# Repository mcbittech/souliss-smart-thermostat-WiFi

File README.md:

# souliss-smart-thermostat-WiFi

Wi-Fi Smart Thermostat based on Souliss IoT Framework

Youtube video:
https://youtu.be/Pk9kK5DvYXE

[Wiki-How to Compile & Upload](https://github.com/mcbittech/souliss-smart-thermostat-WiFi/wiki/SST---WiFi-Souliss-Smart-Thermostat-Wiki)

# Example of SST with 3D printed support & cover:

# Example of layout 2:

# Example of layout 1:

# Example of chrono:

# Bill of Material:
-Olimex ESP8266-EVB  
-ILI9341 with SPI connection, via UEXT connector  
-Rotary Encoder with pushbutton & status LED  
-DHT22 Temperature & Humidity Sensor  

# How to connect your system:

# Power up your system:
All the system require maximum about 200mA @5vdc, with relay ON and maximum brightness of the screen.
Minimum power required about 65mA, with relay OFF and minimum brightness.

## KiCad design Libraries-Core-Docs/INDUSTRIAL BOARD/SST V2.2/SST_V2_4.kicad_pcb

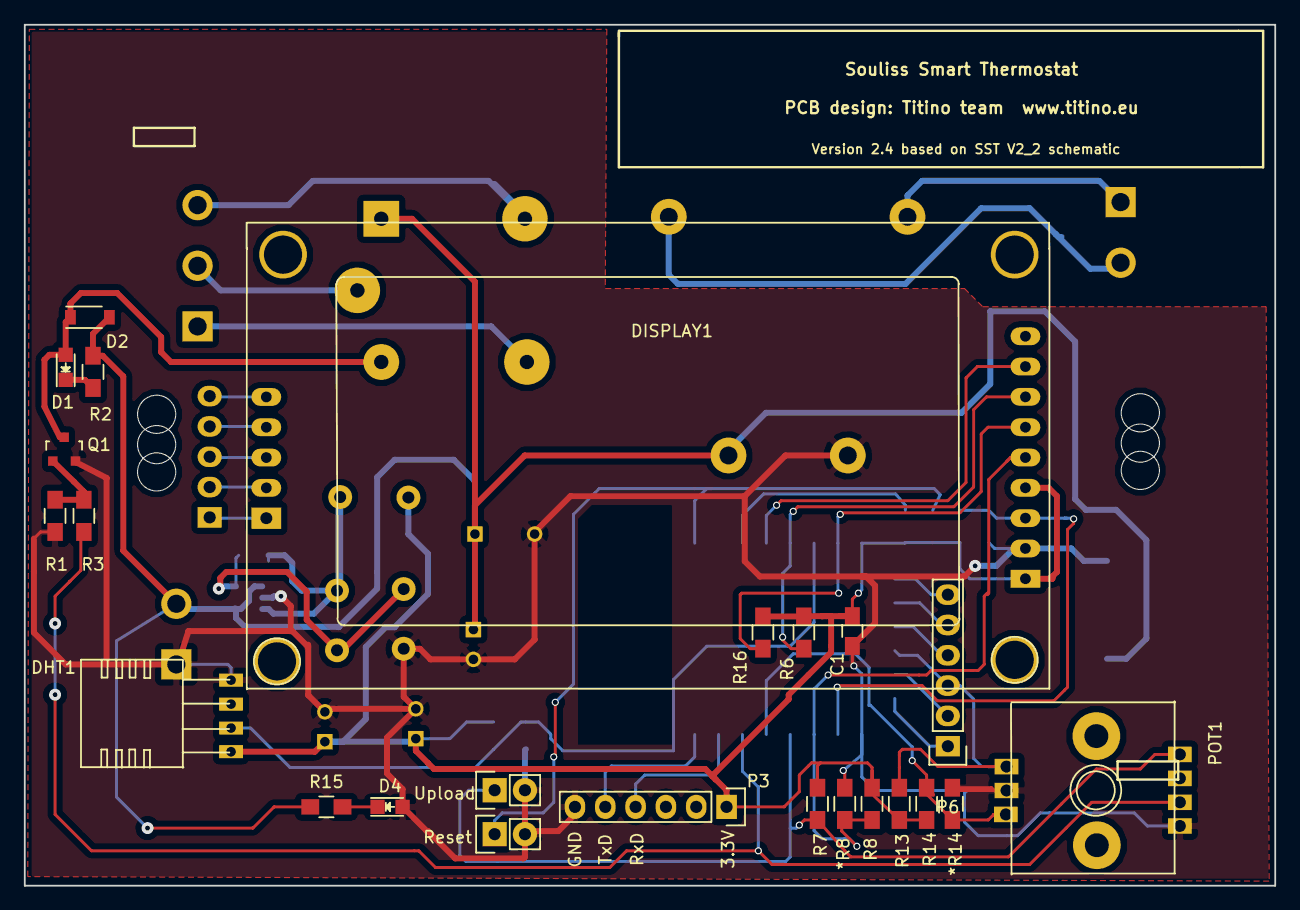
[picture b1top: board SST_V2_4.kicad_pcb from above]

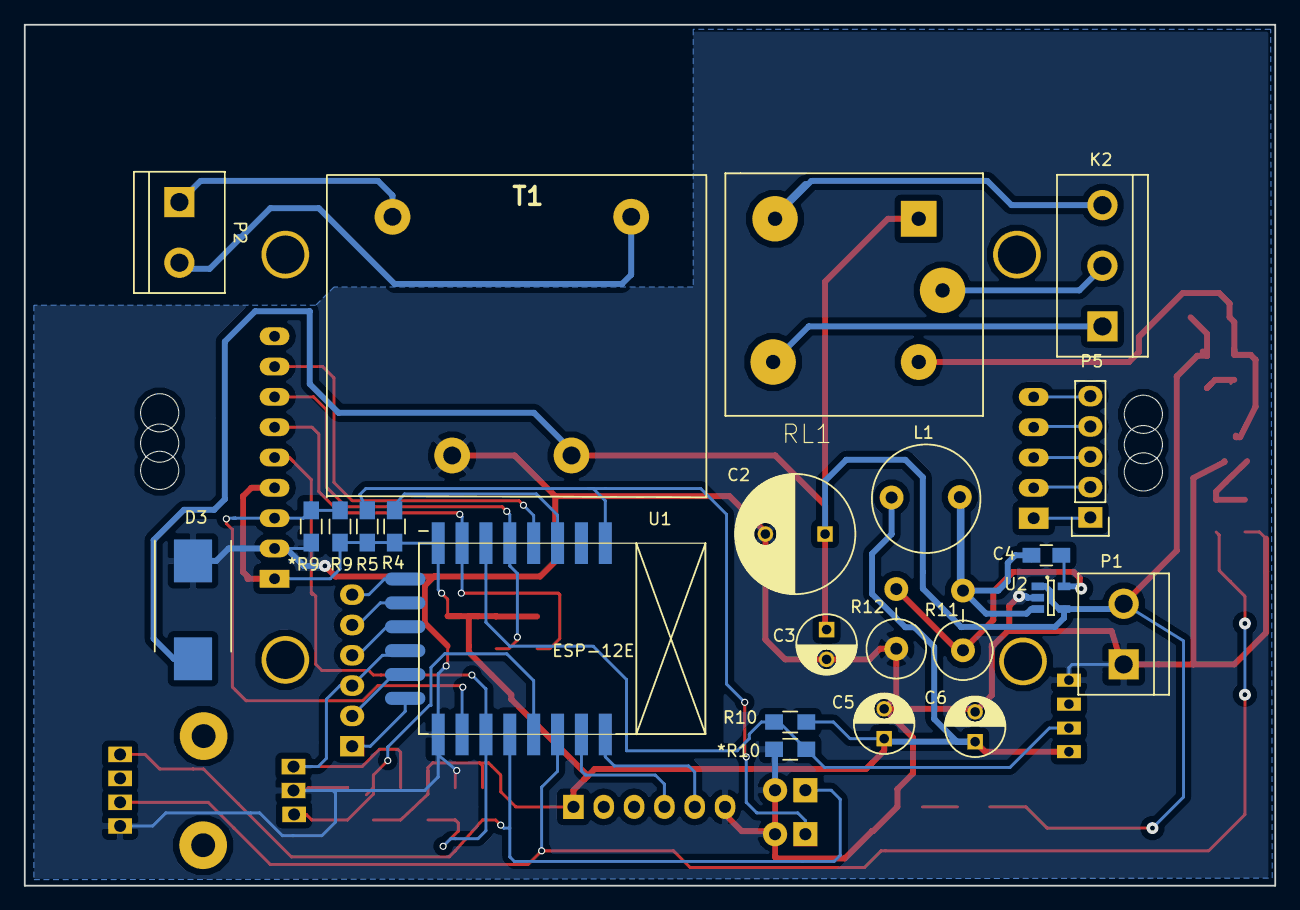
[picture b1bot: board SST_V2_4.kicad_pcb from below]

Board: 2 copper layers, 104.8 x 72.1 mm, 47 parts (23 on the bottom side), 38 nets.

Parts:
*R8, *R14: 2.2k; R_0805_HandSoldering
*R9: 47k; R_0805_HandSoldering
*R10: 10k; R_0805_HandSoldering
C1: 100n; C_0805_HandSoldering
C2: 470u 10V; C_Radial_D10_L21_P5
C3: 22u 16V; C_Radial_D5_L11_P2.5
C4: 22p; C_0805_HandSoldering
C5, C6: 22u 6.3V; C_Radial_D5_L11_P2.5
D1, D4: LED; LED_0805
D2: 1N5819; SOD-123
D3: SMBJ6.0A; DO-214AB_Handsoldering
DHT1: DHT22
DISPLAY1: ILI9341
K2: CONN_3; bornier3
L1: INDUCTOR Murata 1422514C 2.2mH; Choke_Radial_31mm_2.4mm-Drills_CD_Bobin_Type_No1422455
P1, P2: CONN_2; bornier2
P3, P6: CONN_6; Pin_Header_Straight_1x06
P4: CONN_2; Pin_Header_Straight_1x02
P5: CONN_5; Pin_Header_Straight_1x05
POT1: EC12PL; Encoder_potentiometer
Q1: BC818-40; SOT-23
R1, R4: 1k; R_0805_HandSoldering
R2, R7, R8, R15: 2.2k; R_0805_HandSoldering
R3, R5, R6, R10, R13, R14, R16: 10k; R_0805_HandSoldering
R9: 47k; R_0805_HandSoldering
R11: 4.99k 1%; Resistor_Vertical_RM5mm
R12: 1.1k 1%; Resistor_Vertical_RM5mm
RL1: RELAY_1RT; Relay_1RT
SW1: SW_PUSH; Pin_Header_Straight_1x02
T1: VTX-214-005-105
U1: ESP-12E
U2: SY8009A; SOT-23-5

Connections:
3V3: C1.1, C5.1, C6.1, DHT1.1, DISPLAY1.1, DISPLAY1.4, L1.2, P3.1, R4.2, R5.2, R6.2, R7.2, R8.2, R9.2, R10.2, R13.2, R14.2, R16.2, U1.8
+5V: C2.1, C3.1, D2.2, D3.2, P1.2, R2.2, R15.1, RL1.1, T1.4, U2.1, U2.4
/CH_PD: R4.1, U1.3
/GPIO0: P4.1, POT1.4, R7.1, U1.18
/GPIO2: *R8.1, DISPLAY1.5, R8.1, U1.17
/GPIO4: *R14.1, POT1.B, R14.1, U1.19
/GPIO5: POT1.2, R1.1, U1.20
/GPIO10: P6.3, POT1.A, R13.1, U1.12
/GPIO12: *R10.1, DHT1.2, R10.1, U1.6
/GPIO13: DISPLAY1.6, R16.1, U1.7
/GPIO14: DISPLAY1.7, R6.1, U1.5
/GPIO15: *R9.1, DISPLAY1.3, R9.1, U1.16
/GPIO16: DISPLAY1.8, U1.4
/RESET: R5.1, SW1.1, U1.1
/RXD: P3.4, U1.21
/TXD: P3.5, U1.22
GND: *R8.2, *R9.2, *R10.2, *R14.2, C1.2, C2.2, C3.2, C5.2, C6.2, D3.1, D4.2, DHT1.4, DISPLAY1.2, P1.1, P3.6, P4.2, POT1.1, POT1.C, Q1.2, R3.2, R12.1, SW1.2, T1.3, U1.15, U2.2
unnamed: C4.1, L1.1, R11.2, U2.3
unnamed: C4.2, R11.1, R12.2, U2.5
unnamed: D1.1, R2.1
unnamed: D1.2, D2.1, Q1.3, RL1.2
unnamed: D4.1, R15.2
unnamed: DISPLAY1.10, P5.1
unnamed: DISPLAY1.11, P5.2
unnamed: DISPLAY1.12, P5.3
unnamed: DISPLAY1.13, P5.4
unnamed: DISPLAY1.14, P5.5
unnamed: K2.1, RL1.5
unnamed: K2.2, RL1.3
unnamed: K2.3, RL1.4
unnamed: P2.1, T1.2
unnamed: P2.2, T1.1
unnamed: P6.1, U1.14
unnamed: P6.2, U1.13
unnamed: P6.4, U1.11
unnamed: P6.5, U1.10
unnamed: P6.6, U1.9
unnamed: Q1.1, R1.2, R3.1

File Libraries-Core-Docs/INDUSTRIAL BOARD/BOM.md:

## BOM:
| Ref   | Qty  | Value |
|:---------------|:-------------:|:-------------|
|C1       |1 |100n|
|C6,C5    |2 |470n 10v|
|D1       |1 |LED Rosso|
|D2       |1 |1N5819|
|D4       |1 |LED Verde|
|DHT1     |1 |DHT22|
|DISPLAY1 |1 |ILI9341|
|K2       |1 |CONN_3|
|P1,P2,P4 |3 |CONN_2|
|P3,P6    |2 |CONN_6|
|P5       |1 |CONN_5|
|POT1     |1 |EC12PL|
|Q1       |1 |BC818-40|
|R10,R5,*R9,R3,R14,R13,R16,R6  |8 |10k |
|R4,R1    |2 |1k |
|R7,R8,R2,R15  |4 |2.2k |
|RL1      |1 |RELAY_1RT |
|SW1      |1 |SW_PUSH   |
|T1       |1 |VTX-214-005-105 |
|U1       |1 |ESP-12E |
|U2       |1 |LD1085-33 |

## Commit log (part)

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2015-09-14 Add ILI9341 datasheet
2015-09-14 added docs folder
2015-09-15 more docs
2015-09-15 logo
2015-09-15 font first commit
2015-09-15 library correction
2015-09-16 add webconf sketch
2015-09-16 modified name and path
2015-09-16 setpoint to T31. To review precision to 1 decimal.
2015-09-16 arrotondamento da sistemare
2015-09-16 turning around T31 half precision
2015-09-17 Display setpoin with old font ok There is a problem with T31
2015-09-18 simple homescreen
2015-09-19 now Thermostat update immediately T31 Added // Trig the next change of the state data_changed = Souliss_TRIGGED;
    TO DO:
    update display from Souliss T31
2015-09-19 minor change
2015-09-20 sync Thermostat with T31 ok
2015-09-21 Clock NTP OK Refresh NTP every 15 min
2015-09-22 Add copy of library TIME
2015-09-23 revolution on library side
    e04_ESP8266_SST_beta working with souliss framework & new library,
    require replacement of ESP core
2015-09-23 added LED backlite regulation with PWM & analogWrite
2015-09-24 UCGLib integration TODO: SET SIZE AND POSITION
2015-09-24 Add DHT library
2015-09-25 integration with previous menu test sketck
2015-09-27 Add Gitter badge
2015-09-27 display with zone b1..b4 ok To do character °
2015-09-27 Circle Graphics TEST
2015-09-28 added NTP & refresh temperature in SLOW110s
2015-09-28 Flavio Splash screen Rallentati cicli disegno, per avere priorità sull'encoder Da migliorare
2015-09-28 led backlight correction
2015-09-28 encoder with HW interrupt
2015-09-28 deleted void tickEncoder()
2015-09-28 new routine for encoder
2015-09-30 trend Status,Fading LEDbacklight, NTP correction
2015-10-01 Add T19 for dimmer display led 100% on setpoint page
2015-10-02 REPO reorganization
2015-10-02 Add layout connection
2015-10-02 Integration: FADE
2015-10-04 work in progress. Do not compile
2015-10-05 Improved trend medium
2015-10-06 var correction
2015-10-06 test new git client
2015-10-06 Working selection days on program menù
2015-10-06 comment correction
2015-10-06 Working selection days on program menù less code
2015-10-07 Improvement chrono matrix array
2015-10-08 SPI.setFrequency(40000000);
2015-10-08 other improvement on chrono, setpoint setting(work in progress)
2015-10-08 work in progress TODO: - background colors - Flavio codes
2015-10-10 working on chrono
2015-10-15 Write setpoint number over bargraph on chrono
2015-10-26 need configuration in 3 lines
2015-10-27 Second layout ok
2015-10-27 Two layouts ok
    Configurable in file layouts.h
2015-10-27 Added copy of menusystem Library
2015-10-28 bugfix fade
2015-10-28 Menu - Structure
2015-10-28 Working on Layout 2, animation of circle
2015-10-28 working
2015-10-29 Mod to LAYOUT_1 Click to clean screen and print menu on serial monitor
2015-10-30 Added images for users
2015-10-30 one more image
2015-10-30 Added video for users
2015-11-05 Navigazione ok, uscita menu ok
2015-11-06 work in progress
2015-11-07 bug fix
2015-11-07 Display bright ok
2015-11-10 work in progress To review TEXT "SPENTO"
2015-11-16 system ON/OFF on display. To test
2015-11-16 System ON/FF on display ok
2015-12-07 changed directories structures
2015-12-07 Problem with SPI Frequency. Ok
2015-12-27 Recovery scheme folder file
2015-12-27 Link correction, issue #3
2016-01-19 Upgrade version to 0.8 Add OTA name
2016-02-04 Added serial.print for debug
2016-02-04 debug info addiction
2016-02-04 Increase SPI speed Delete debug line Beta Testing version for NTP & Layout2 issue
2016-02-04 Add Flavio files
2016-02-11 Added PCB layout
2016-02-16 Added 1 boxes(setpoint) on chrono, now 4 setpoint are available
2016-02-16 System ON/OFF - It seem Ok Some user preferences in separate file preferences.h
2016-02-16 Updated version number to 0.9
    Crono item in first page only if it is enable on preferences.h
2016-02-16 Added eeprom read/save. BETA TEST version
2016-02-16 added function read_save in eeprom
2016-02-17 Offset for flash eeprom
2016-02-17 Eeprom function correction
2016-02-17 Added eeprom settings save
2016-02-18 Do not compile ??Store_Init() ??
2016-02-18 It compile. To do test
2016-02-19 Now it work.
    Commented code for read in EEPROM
2016-02-21 eeprom correction + chrono read/save data from eeprom
2016-02-21 working on navigation inside chrono
2016-02-22 Added color on setpoint + bar Improved navigation on crono Added refresh for visualization of day bar
2016-02-23 Hook crono data from NTP Time -beta minor bugfixes(eeprom float setpoint, colour, days sequence)
2016-02-23 Added debug info for crono
2016-02-23 another bugfix
2016-02-24 Now it compile in IDE 1.6.7
2016-02-24 Crono Sp active in home screen
2016-02-24 Setpoint change with crono OK
2016-02-26 working on crono....
2016-02-26 working eeprom
2016-02-26 Branch start Recover topic published from nodes or gateway
2016-02-27 enhancement crono
2016-02-29 longpress + colour setpoin homepage visualisation
2016-02-29 days + save visualization fix
2016-02-29 working....
2016-02-29 bkp copy crono working + navigation + eeprom
2016-02-29 library
2016-02-29 Added static IP option(thanks to Dariocdj) Fixed menù navigation + crono navigation
2016-03-01 added menù for timezone NTP clock(thanks Dariocdj)
2016-03-02 Now is possible to select time Zone on NTP from menù. Your selection is stored in eeprom.
2016-03-02 Added first start from preferences, then from eeprom
2016-03-02 bug correction for commit 362098f74123896f8e630132e0800989ccdb50a1
2016-03-02 bugfix displaybright
2016-03-02 Publish&Subcribe OK work in progress
2016-03-02 OTA webupdater fix
    It don't work with actual ESP Core
2016-03-03 displaybright bugfix try to solve setpoint bug on crono
2016-03-03 Static IP bugfix
2016-03-03 working with setpoint
2016-03-03 working on crono navigation
2016-03-03 bugfix navigation crono + setpoint :)
2016-03-03 working on crono
2016-03-03 bypass delay for switch
2016-03-03 Added text system state in homepage
2016-03-03 working on system state + setpoint crono navi
2016-03-03 added copy/paste function Now is possible to copy your settings of any day on crono and paste it in another day
2016-03-03 description correction
2016-03-03 version change now V0.21
2016-03-04 improving log + refresh setpoint
2016-03-04 log enhancement
2016-03-04 version change now 0.22 BETA
2016-03-05 new photos
2016-03-05 photo size + layout1 in readme
2016-03-06 WORK IN PROGRESS
    MODIFIED SetThermostatON for new T31 bugfix of Souliss Framework
2016-03-07 Update readme with youtube video
2016-03-08 heating/cooling bit changed
    New thermostat ON function!!!
2016-03-08 Good.
2016-03-10 Topics Page ok To adjust, float to int when decimals == 00
2016-03-21 Sembra ok
2016-03-24 Button click fixed
2016-03-24 VERSION "v0.4"
2016-03-26 EEPROM offset moved to 500
2016-04-19 preferences Tonino
2016-04-20 ignore preferences.h
2016-05-25 Compilazione con IDE 1.6.8 e ESP core 2.2.0
    Non compila la libreria menusystem
2016-05-29 aggiunte librerie adatte e spostate nella cartella libraries
2016-06-02 Now ArduinoOta work!!
    Flash Mode DIO
    Flash frequency 40 MHz
    CPU frequency 160 MHz
    Flash size: 1Mb (64K SPIFFS)
    Autoconfiguration Mode don't work
2016-06-02 default: DHCP ON DYNAMIC MODE OFF
2016-06-09 Issue Menu responsive #20 https://github.com/mcbittech/souliss-smart-thermostat-WiFi/issues/20
    Resa più reattiva la navigazione del menu
2016-06-09 test Mod Dario with some adjustement
2016-06-12 #define VERSION "v0.85"
2016-06-13 modifiche Dario - Attesa revisione e merge
2016-06-13 ...for merge
2016-08-13 isNan control for temperature and humidity
2016-08-14 inclusion of multiClick library
2016-08-14 support for double click, hold, long hold
2016-08-15 child lock function
2016-08-17 Some mod to OTA - Testing
2016-08-17 Ver 0.9
2016-08-17 bugfix
2016-08-17 Topics Pages optimization
2016-08-18 some bugfix for Layout2
2016-08-21 Topics Alignment
2016-09-11 Menu: EEPROM_Reset and spiffs_Reset
2016-09-21 added library ArduinoJson
2016-09-21 Update with wiki link
2016-09-27 NTP correction, in testing issue #31
2016-09-27 new_mod_dcdj
    solved issue:
    #30
    #29
    #28
    #17
    #15
2016-09-28 NTP, working on
2016-10-02 Publish message HEAT ON or OFF #define SST_HEAT_ONOFF 0xF001,0x0B U8 HEAT_ON = 0X01; U8 HEAT_OFF = 0X00;
2016-10-07 solve issue #33
2016-10-28 Avanzamento a versione 1.0
    Logica Termostato e T52 inseriti nello stesso ciclo FAST_510ms()
    Prima erano temporizzati diversamente ed a volte sembravano esserci disallineamenti tra i due valori letti da SoulissApp e Openhab
2016-11-02 new souliss names for subscribedata and publishdata: sbscrbdata and pblshdata
2016-11-18 revert to original :-(
2016-11-21 remove old EEPROM and EPS8266WebServer.h
2016-11-21 revolution with asyncwebserver :-) bugfixes on calling of Time library
2016-11-21 integration with async WBServer
2016-11-21 new version 1.2
2016-11-21 major variable integration,we take some days to test, it seems too slow only in some operation...
2016-11-22 variable name normalization
2016-11-23 remove some comment
2016-11-23 S_relestatus_WBS bug correction first release datalogger to sst_datalogger.csv
2016-11-23 datalogger frequency about 10min now datalogger append new value :-) todo: deleting old values to mantain specified size of file
2016-11-23 remove old directory
2016-11-24 solved bug on B_is_away_WBS & B_away_WBS
2016-11-24 changed path datalogger to /datalog/sst_datalogger.csv bug correction on datatype of S_relestatus_WBS
2016-11-30 init value WBS, for testing purpose
2016-12-03 nostname bug correction
2016-12-03 //new customs Souliss_T3n_DeadBand and Souliss_T3n_Hysteresis
    Need update of Souliss Libraries (only file Typicals.h)
2016-12-05 patch with yield() on crono while
    it seems to be an overflow bug on buffer of SDK, on WiFi code
2016-12-11 wbserver SST side correction
2016-12-12 e06_ESP_SST_RemoteHeatingRelay example
    example of remote relay node
2016-12-13 datalogger mod, now one file as per day is created, last week remain in spiffs, after one week file will be overwritten. Now the complete path/name of files are: /datalog/sst_dataloggerX.csv where X 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
2016-12-14 webserver, added delay on save
2016-12-14 trigger for Away function and powerfull function away is also available from AWAY_SLOT for Souliss side
2016-12-14 Away function + Powerfull function Away is Sp0(minimum setpoint on crono) + Sp6(dedicated offset) Powerfull is Sp3(maximum setpoint on crono) + Sp7(dedicated offset)
2016-12-14 now you can choose from a relative setpoint or a relative setpoint for Away & Powerfull functions relative work as described in commit 894c7b50be8f5a43a61246de4842f62aa0c2bded fixed set Sp6 value for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
2016-12-16 testing purpose
2016-12-20 TTD alpha function
2016-12-20 TTD, now you can exclude it
2016-12-21 TTD improvement for serial debug
2016-12-23 try to solve webserver crash error: scrivo file: sst_crono_matrix.json{"Sp0":18.00,"Sp1":20.00,"Sp2":21.50,"Sp3":23.00,"cronomatrix":[0,2,2,0,0,3,4,4,4,4,4,3,0,0,0,0,0,0,0,3,0,0,0,0,0,1,2,0,1,0,0,0,0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
2016-12-23 added preference "master" file you must configure it and rename in preferences.h
2016-12-27 libraries reorganization
2016-12-29 debug option crono with #define DEBUG #define DEBUG_DEV
2016-12-29 debug option datalogger with #define DEBUG #define DEBUG_DEV
2016-12-29 debug option display with #define DEBUG #define DEBUG_DEV
2016-12-29 more clean code encoder.cpp
2016-12-29 debug option menu with #define DEBUG #define DEBUG_DEV
2016-12-29 debug option read_save with #define DEBUG #define DEBUG_DEV
2016-12-29 debug option setup_OTA_WBServer with #define DEBUG #define DEBUG_DEV
2016-12-29 debug option e05_ESP8266_SST_webconf with #define DEBUG #define DEBUG_DEV
2016-12-29 missing #include "preferences.h"
2017-01-19 Added Offset for DHT sensor
2017-01-30 correction on webserver files
2017-01-30 adding user authentication for webserver
2017-01-30 webserver improvement
2017-10-11 Fixed connection dynamic and static too
2017-10-11 PCB Fritzing Version
    Here is my Homemade PCB Version made with Fritzing
2017-11-22 test with Eclipse, compile ok
2017-11-22 use bright() function instead of digitalwrite for analog backlight
2017-11-22 working on issue #40
2017-12-28 errata corrige pcb project
2017-12-28 add some cover photos
2017-12-28 update readme with some cover photos
